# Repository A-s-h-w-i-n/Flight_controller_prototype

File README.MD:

First version of a PCB designe for a flight controller for model aircrafts and drones. 
The system has been developed around the Arduino Nano microcontroller board. The developer can develop 
and implement different control algorithms for flight control on this board. The PCB has been designed 
to accomodate the following:
1) Arduino Nano
2) GY-87 (or GY-86) sensor (Consists of MPU6050 (3-axis Gyro + 3-axis Acceleration), 
   HMC5883L (3-axis Magnetic Field), BMP180 (Air Pressure Sensor)
3) MP-1584 mini buck converter

There are extension pads for the following:
1) 6 PWM outputs
2) PWM pin D3 can be used as ext interrupt pin
3) GPS module (pins D7 & D8)
4) Hardware serial for serial transceiver
5) Extra I2C slot
6) Analog i/o pin A0

2 x 1206 size 4.7K ohm resistor have to be added as pull up resistors on the I2C lines.

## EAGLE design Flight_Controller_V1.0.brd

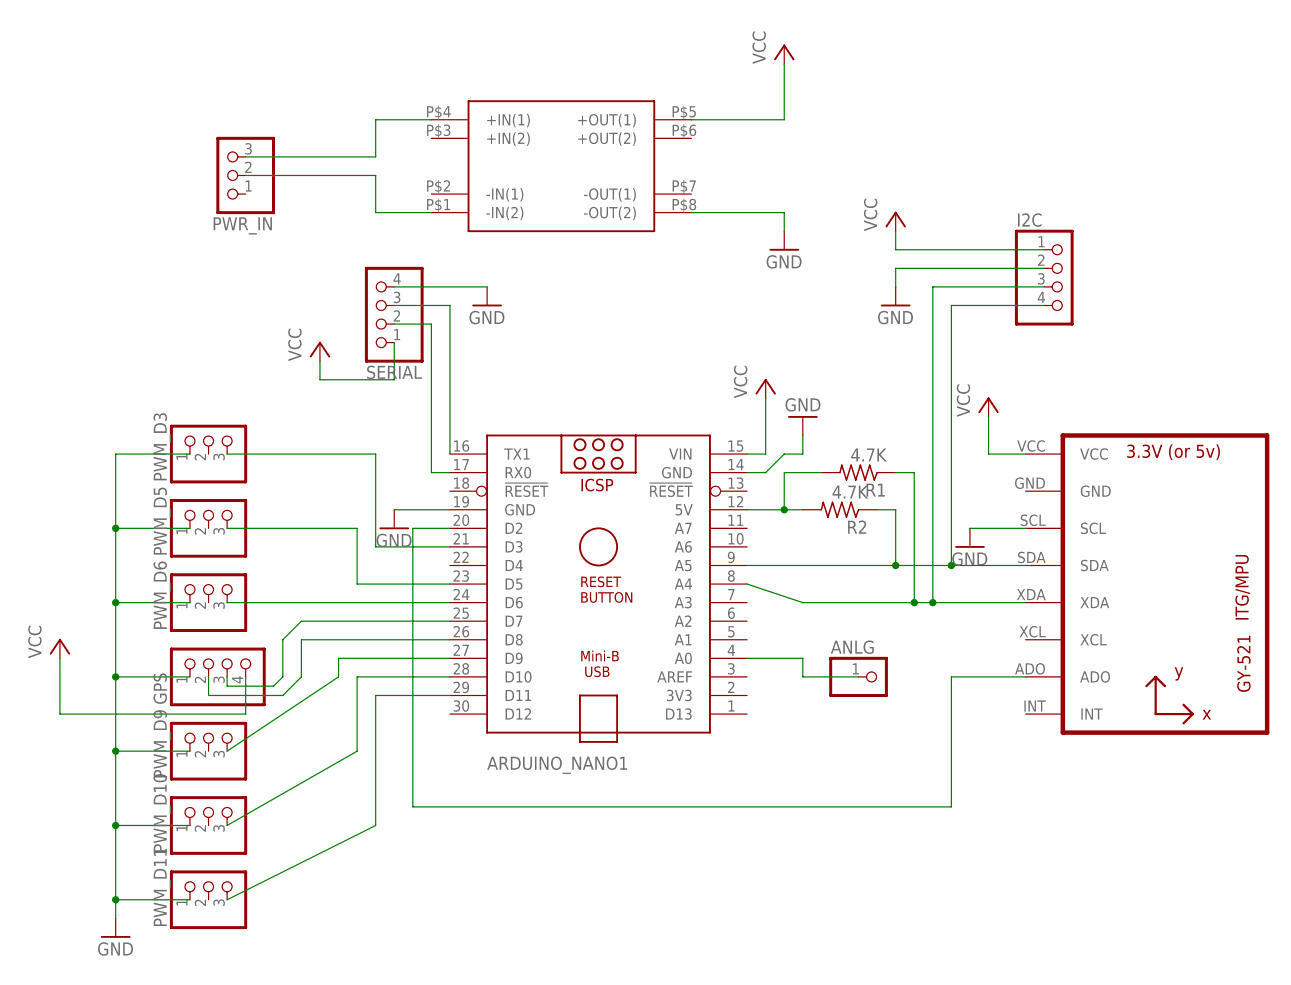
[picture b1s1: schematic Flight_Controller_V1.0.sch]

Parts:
ANLG: PINHD-1X1; 1X01
ARDUINO_NANO1: ARDUINO_NANO
GPS: PINHD-1X4; 1X04
I2C: PINHD-1X4; 1X04
PWM_D3, PWM_D5, PWM_D6, PWM_D9, PWM_D10, PWM_D11: PINHD-1X3; 1X03
PWR_IN: PINHD-1X3; 1X03
R1, R2: 4.7K; R1206
SERIAL: PINHD-1X4; 1X04
U1: GY-521MPU6050; GY-521
U$1: MP1584_DEVICETHROUGH_HOLE; MP1584_PACKAGE

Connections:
GND: ARDUINO_NANO1.14 (GND), ARDUINO_NANO1.19 (GND), GPS.1, I2C.2, PWM_D3.1, PWM_D5.1, PWM_D6.1, PWM_D9.1, PWM_D10.1, PWM_D11.1, SERIAL.4, U1.SCL, U$1.P$8 (-OUT(2))
unnamed: ARDUINO_NANO1.17 (RX0), SERIAL.2
unnamed: ARDUINO_NANO1.16 (TX1), SERIAL.3
unnamed: ARDUINO_NANO1.20 (D2), U1.ADO
unnamed: PWR_IN.3, U$1.P$4 (+IN(1))
unnamed: ARDUINO_NANO1.12 (5V), R1.2, R2.2
unnamed: PWR_IN.2, U$1.P$1 (-IN(2))
unnamed: ARDUINO_NANO1.21 (D3), PWM_D3.3
unnamed: ARDUINO_NANO1.23 (D5), PWM_D5.3
unnamed: ARDUINO_NANO1.24 (D6), PWM_D6.3
unnamed: ARDUINO_NANO1.27 (D9), PWM_D9.3
unnamed: ARDUINO_NANO1.28 (D10), PWM_D10.3
unnamed: ARDUINO_NANO1.29 (D11), PWM_D11.3
unnamed: ANLG.1, ARDUINO_NANO1.4 (A0)
unnamed: ARDUINO_NANO1.25 (D7), GPS.3
unnamed: ARDUINO_NANO1.26 (D8), GPS.2
SCL: ARDUINO_NANO1.9 (A5), I2C.4, R2.1, U1.SDA
SDA: ARDUINO_NANO1.8 (A4), I2C.3, R1.1, U1.XDA
VCC: ARDUINO_NANO1.15 (VIN), GPS.4, I2C.1, SERIAL.1, U1.VCC, U$1.P$5 (+OUT(1))

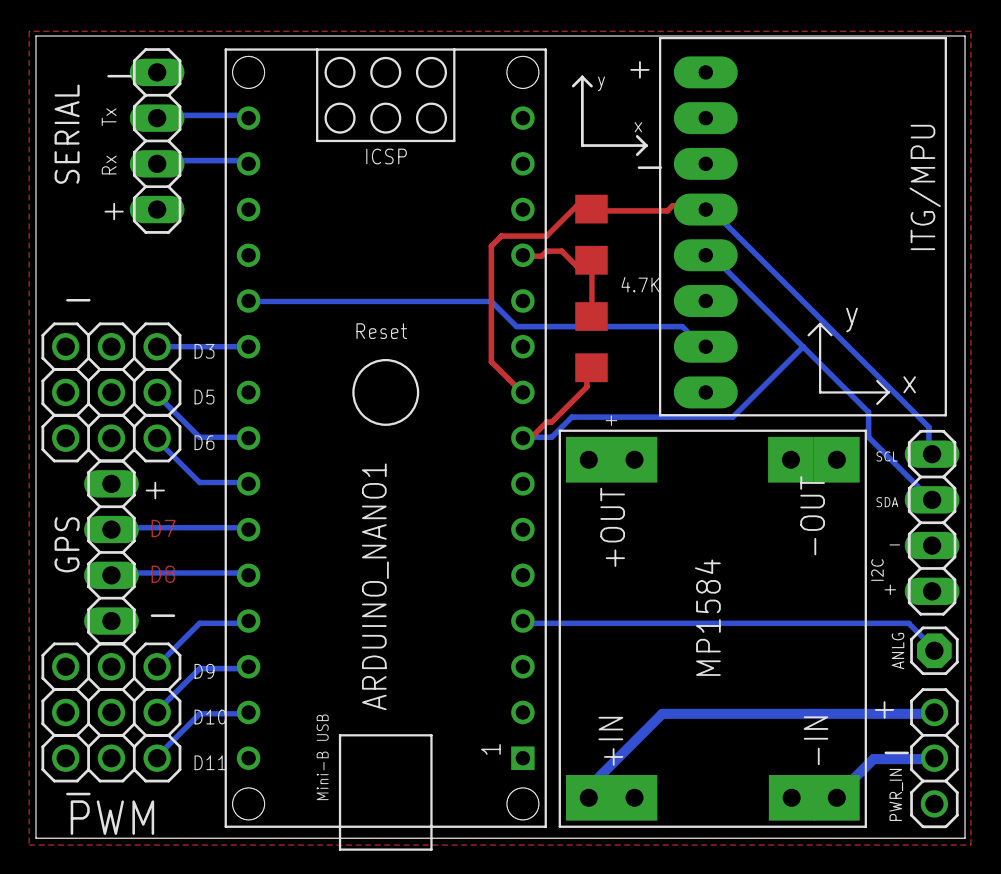
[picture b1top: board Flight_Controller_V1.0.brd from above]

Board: 2 copper layers, 51.6 x 44.6 mm, 16 parts (0 on the bottom side), 19 nets.

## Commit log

2019-06-21 :confetti_ball: Added .gitattributes & .gitignore files
2019-06-21 V1.0
    A compact PCB design to accomodate a flight controller based on the
    Arduino Nano for prototyping control systems.
